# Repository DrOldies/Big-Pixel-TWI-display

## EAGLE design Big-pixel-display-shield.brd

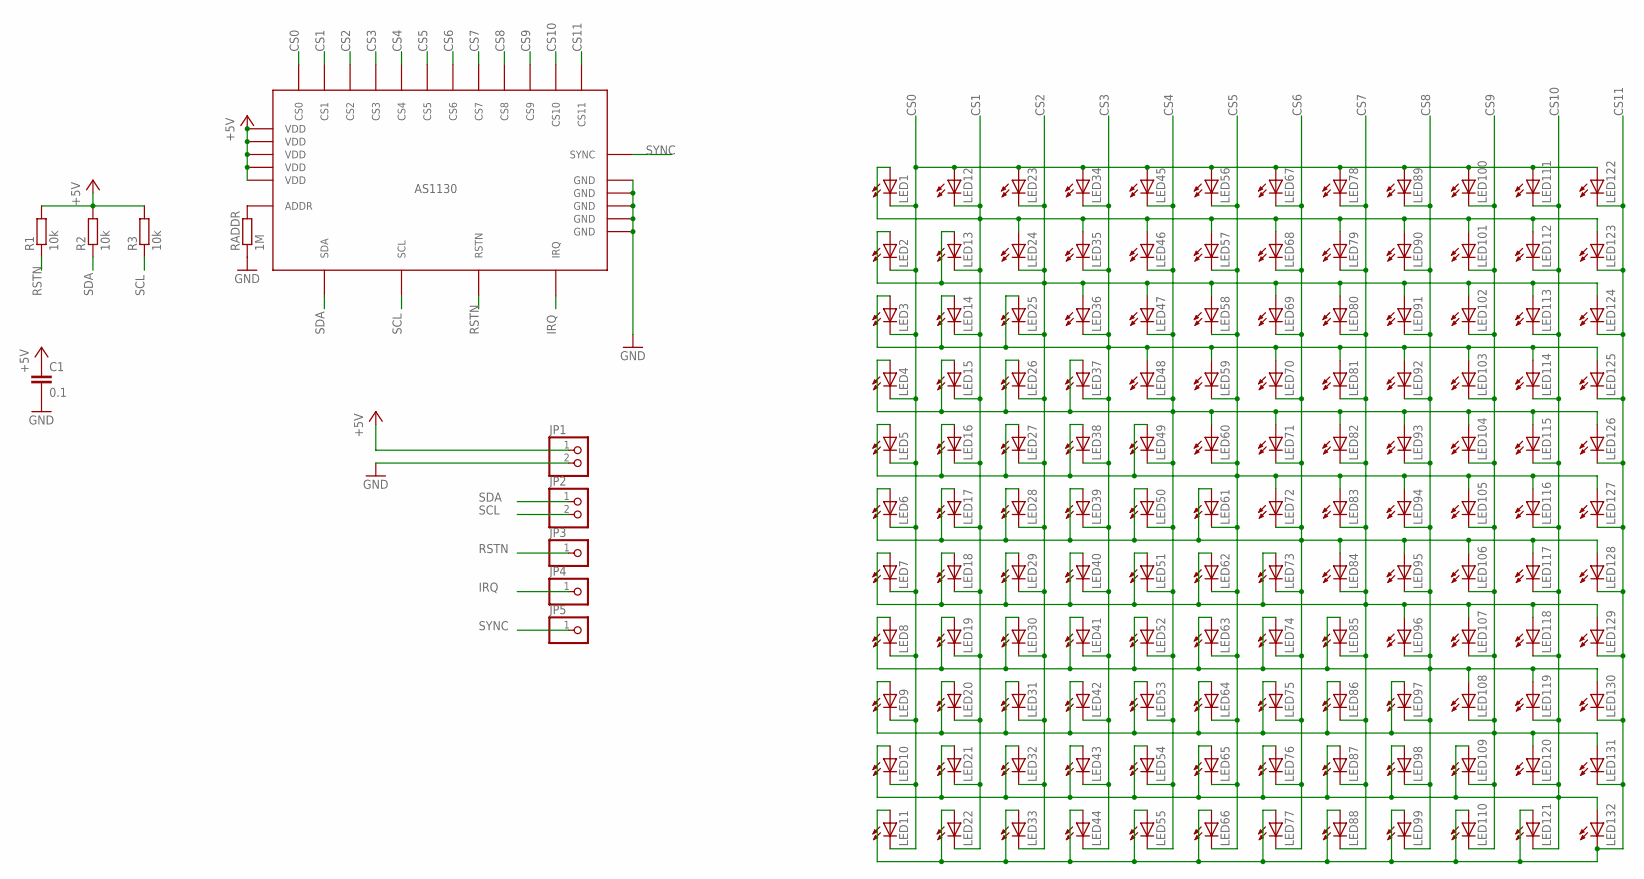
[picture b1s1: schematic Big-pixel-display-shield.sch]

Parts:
C1: 0.1; C0805
JP1, JP2: PINHD-1X2; 1X02
JP3, JP4, JP5: PINHD-1X1; 1X01
LED1, LED2, LED3, LED4, LED5, LED6, LED7, LED8, LED9, LED10, LED11, LED12, LED13, LED14, LED15, LED16, LED17, LED18, LED19, LED20, LED21, LED22, LED23, LED24, LED25, LED26, LED27, LED28, LED29, LED30, LED31, LED32, LED33, LED34, LED35, LED36, LED37, LED38, LED39, LED40, LED41, LED42, LED43, LED44, LED45, LED46, LED47, LED48, LED49, LED50, LED51, LED52, LED53, LED54, LED55, LED56, LED57, LED58, LED59, LED60, LED61, LED62, LED63, LED64, LED65, LED66, LED67, LED68, LED69, LED70, LED71, LED72, LED73, LED74, LED75, LED76, LED77, LED78, LED79, LED80, LED81, LED82, LED83, LED84, LED85, LED86, LED87, LED88, LED89, LED90, LED91, LED92, LED93, LED94, LED95, LED96, LED97, LED98, LED99, LED100, LED101, LED102, LED103, LED104, LED105, LED106, LED107, LED108, LED109, LED110, LED111, LED112, LED113, LED114, LED115, LED116, LED117, LED118, LED119, LED120, LED121, LED122, LED123, LED124, LED125, LED126, LED127, LED128, LED129, LED130, LED131, LED132: LED5MM
R1, R2, R3: 10k; R1206
RADDR: 1M; R1206
U$1: AS1130; SSOP28

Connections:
+5V: C1.1, JP1.1, R1.2, R2.2, R3.2, U$1.3 (VDD), U$1.10 (VDD), U$1.18 (VDD), U$1.19 (VDD), U$1.26 (VDD)
CS0: LED1.K (C), LED2.K (C), LED3.K (C), LED4.K (C), LED5.K (C), LED6.K (C), LED7.K (C), LED8.K (C), LED9.K (C), LED10.K (C), LED11.K (C), LED12.A, LED23.A, LED34.A, LED45.A, LED56.A, LED67.A, LED78.A, LED89.A, LED100.A, LED111.A, LED122.A, U$1.25 (CS0)
CS1: LED1.A, LED12.K (C), LED13.K (C), LED14.K (C), LED15.K (C), LED16.K (C), LED17.K (C), LED18.K (C), LED19.K (C), LED20.K (C), LED21.K (C), LED22.K (C), LED24.A, LED35.A, LED46.A, LED57.A, LED68.A, LED79.A, LED90.A, LED101.A, LED112.A, LED123.A, U$1.27 (CS1)
CS2: LED2.A, LED13.A, LED23.K (C), LED24.K (C), LED25.K (C), LED26.K (C), LED27.K (C), LED28.K (C), LED29.K (C), LED30.K (C), LED31.K (C), LED32.K (C), LED33.K (C), LED36.A, LED47.A, LED58.A, LED69.A, LED80.A, LED91.A, LED102.A, LED113.A, LED124.A, U$1.23 (CS2)
CS3: LED3.A, LED14.A, LED25.A, LED34.K (C), LED35.K (C), LED36.K (C), LED37.K (C), LED38.K (C), LED39.K (C), LED40.K (C), LED41.K (C), LED42.K (C), LED43.K (C), LED44.K (C), LED48.A, LED59.A, LED70.A, LED81.A, LED92.A, LED103.A, LED114.A, LED125.A, U$1.24 (CS3)
CS4: LED4.A, LED15.A, LED26.A, LED37.A, LED45.K (C), LED46.K (C), LED47.K (C), LED48.K (C), LED49.K (C), LED50.K (C), LED51.K (C), LED52.K (C), LED53.K (C), LED54.K (C), LED55.K (C), LED60.A, LED71.A, LED82.A, LED93.A, LED104.A, LED115.A, LED126.A, U$1.21 (CS4)
CS5: LED5.A, LED16.A, LED27.A, LED38.A, LED49.A, LED56.K (C), LED57.K (C), LED58.K (C), LED59.K (C), LED60.K (C), LED61.K (C), LED62.K (C), LED63.K (C), LED64.K (C), LED65.K (C), LED66.K (C), LED72.A, LED83.A, LED94.A, LED105.A, LED116.A, LED127.A, U$1.20 (CS5)
CS6: LED6.A, LED17.A, LED28.A, LED39.A, LED50.A, LED61.A, LED67.K (C), LED68.K (C), LED69.K (C), LED70.K (C), LED71.K (C), LED72.K (C), LED73.K (C), LED74.K (C), LED75.K (C), LED76.K (C), LED77.K (C), LED84.A, LED95.A, LED106.A, LED117.A, LED128.A, U$1.2 (CS6)
CS7: LED7.A, LED18.A, LED29.A, LED40.A, LED51.A, LED62.A, LED73.A, LED78.K (C), LED79.K (C), LED80.K (C), LED81.K (C), LED82.K (C), LED83.K (C), LED84.K (C), LED85.K (C), LED86.K (C), LED87.K (C), LED88.K (C), LED96.A, LED107.A, LED118.A, LED129.A, U$1.4 (CS7)
CS8: LED8.A, LED19.A, LED30.A, LED41.A, LED52.A, LED63.A, LED74.A, LED85.A, LED89.K (C), LED90.K (C), LED91.K (C), LED92.K (C), LED93.K (C), LED94.K (C), LED95.K (C), LED96.K (C), LED97.K (C), LED98.K (C), LED99.K (C), LED108.A, LED119.A, LED130.A, U$1.5 (CS8)
CS9: LED9.A, LED20.A, LED31.A, LED42.A, LED53.A, LED64.A, LED75.A, LED86.A, LED97.A, LED100.K (C), LED101.K (C), LED102.K (C), LED103.K (C), LED104.K (C), LED105.K (C), LED106.K (C), LED107.K (C), LED108.K (C), LED109.K (C), LED110.K (C), LED120.A, LED131.A, U$1.6 (CS9)
CS10: LED10.A, LED21.A, LED32.A, LED43.A, LED54.A, LED65.A, LED76.A, LED87.A, LED98.A, LED109.A, LED111.K (C), LED112.K (C), LED113.K (C), LED114.K (C), LED115.K (C), LED116.K (C), LED117.K (C), LED118.K (C), LED119.K (C), LED120.K (C), LED121.K (C), LED132.A, U$1.9 (CS10)
CS11: LED11.A, LED22.A, LED33.A, LED44.A, LED55.A, LED66.A, LED77.A, LED88.A, LED99.A, LED110.A, LED121.A, LED122.K (C), LED123.K (C), LED124.K (C), LED125.K (C), LED126.K (C), LED127.K (C), LED128.K (C), LED129.K (C), LED130.K (C), LED131.K (C), LED132.K (C), U$1.8 (CS11)
GND: C1.2, JP1.2, RADDR.1, U$1.1 (GND), U$1.7 (GND), U$1.14 (GND), U$1.22 (GND), U$1.28 (GND)
IRQ: JP4.1, U$1.11 (IRQ)
unnamed: RADDR.2, U$1.17 (ADDR)
RSTN: JP3.1, R1.1, U$1.13 (RSTN)
SCL: JP2.2, R3.1, U$1.15 (SCL)
SDA: JP2.1, R2.1, U$1.16 (SDA)
SYNC: JP5.1, U$1.12 (SYNC)

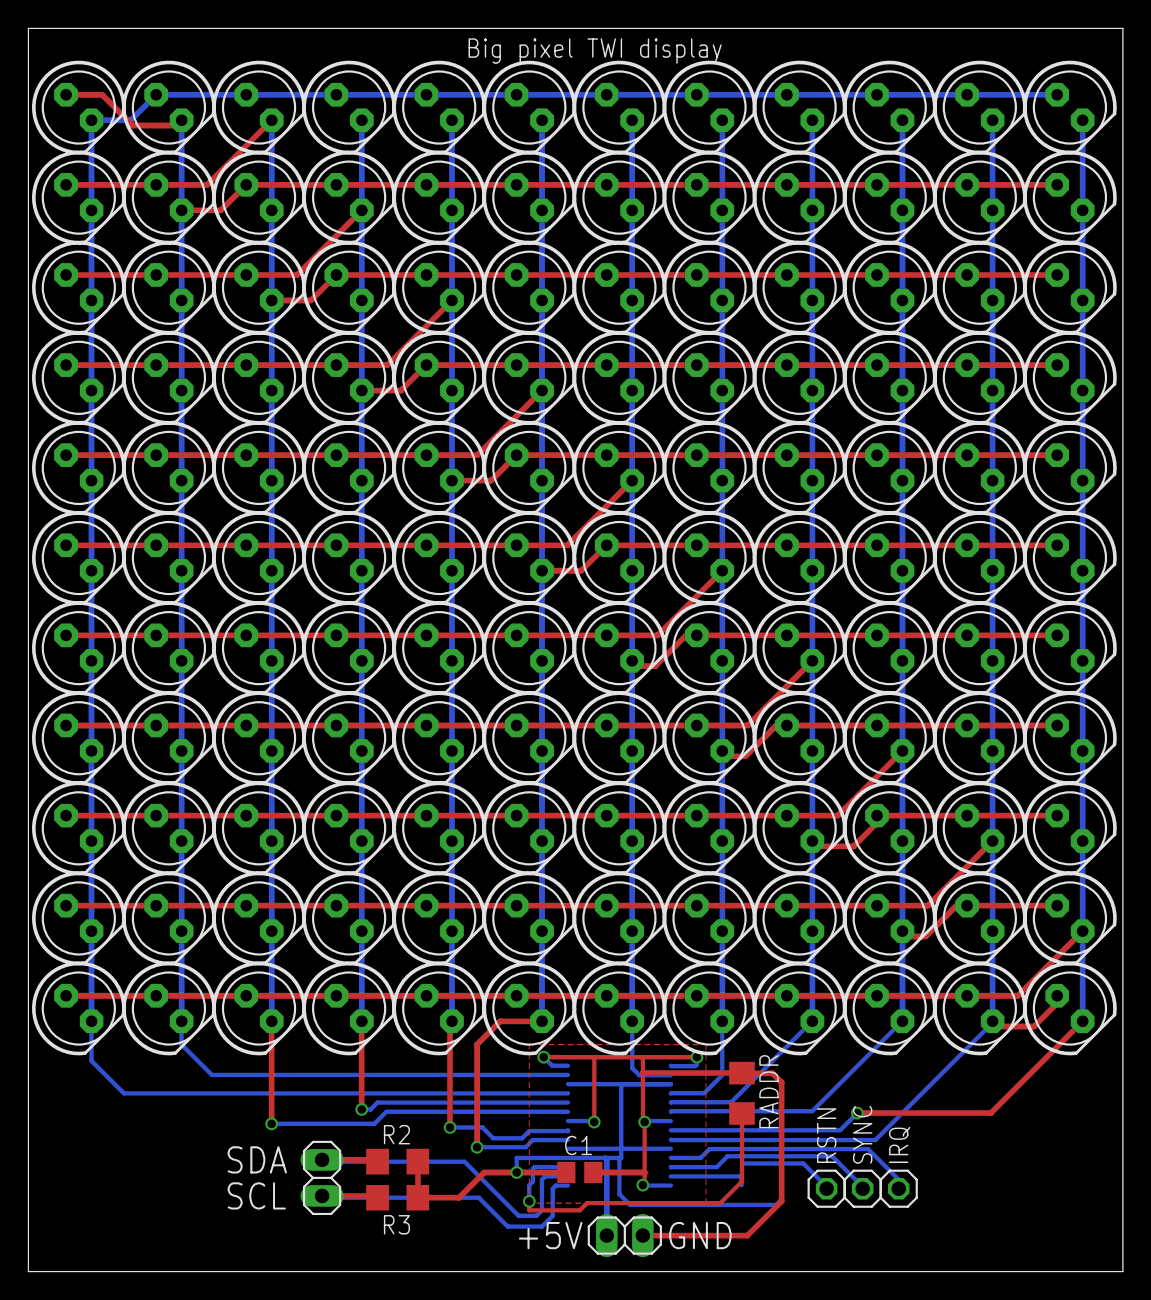
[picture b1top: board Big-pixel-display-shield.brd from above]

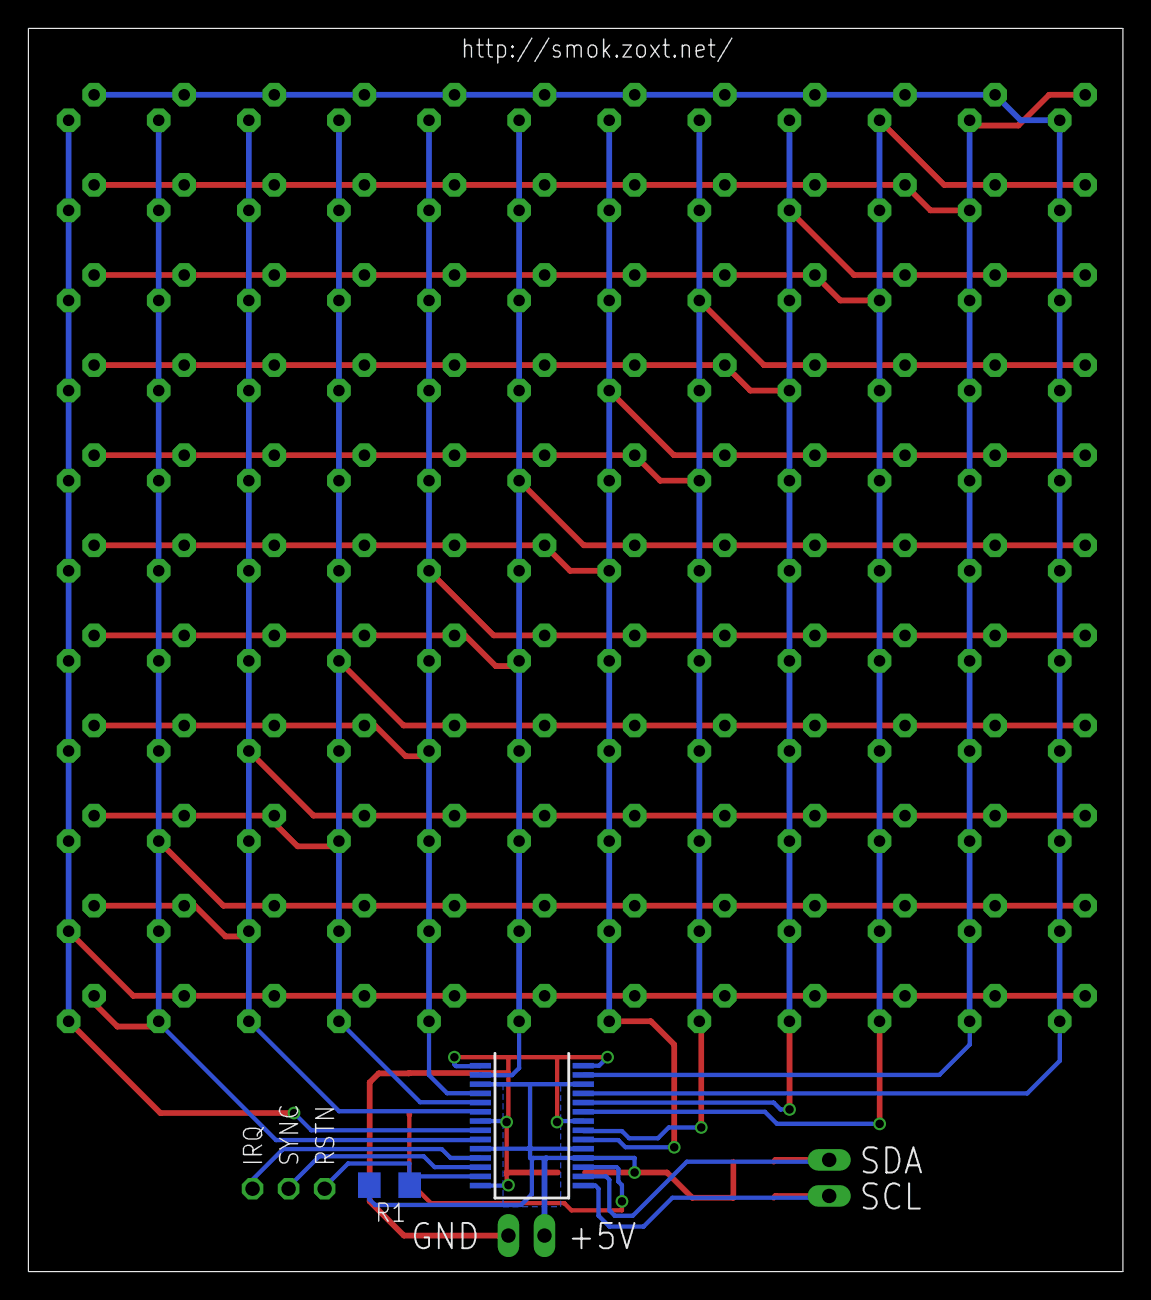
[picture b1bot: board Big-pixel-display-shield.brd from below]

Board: 2 copper layers, 77.1 x 87.6 mm, 143 parts (2 on the bottom side), 20 nets.
